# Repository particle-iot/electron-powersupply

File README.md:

Electron Power Management
---
[Place to host the experimental power supply design files for the Electron]

> To put it simply, the challenge in designing the power supply unit for the Electron is _supply and demand_. 

A cellular module is a power hungry device. Unlike WiFi, a GSM module requires a higher burst of power during transmission. These power/current spikes can go as high as 2Amps. This clearly exceeds USB's limit of 500mA in most cases. When developing on the Electron connected to a computer, care must be taken not to exceed the USB's limit while maintaining uninterrupted power to the cellular module. Most portable devices overcome this by having a battery connected at all times, like mobile phones. For a device like the Electron, it becomes essential to have the flexibility to power it either via the USB, battery or both.

The USB powered GSM modems currently available in the market use a switch-mode DC regulator with a high capacity bulk capacitor at the output. This capacitor stores enough energy to power the GSM module during its peak power requirements. At the same time, the regulator makes sure not to exceed the 500mA limit of draw current from a USB port. Most of the USB ports on today's computers are capable of sourcing 1Amp of continuous current. This allows for the use of a smaller bulk capacitor, but you still need to use one.

Things get a little interesting when you consider that 2G and 3G power requirements are completely different. The main difference is that a 2G TX burst will consume upto 2Amp of peak current, while in 3G burst is more controllable and flat with a peak requirement of 0.8A.

**Potential setup for the power unit:**

**Requirements for the PMC:**
 - Programmable input current limit
 - Built-in charger for 3.7V LiPo
 - Ouput current of minimum 1A
 - Power path management (optional)
 - Build-in switcher (optional)
 - Small footprint

**List of ICs under evaluation:**
- [BQ24298] (http://www.ti.com/lit/ds/symlink/bq24298.pdf) complete PMC from TI
- [LTC3567] (http://cds.linear.com/docs/en/datasheet/3567f.pdf) compete PMC from LT
- [BQ24030] (http://www.ti.com/lit/ds/symlink/bq24030.pdf) complete PMC - currently used on the power shield
- [TPS62750] (http://www.ti.com/lit/ds/symlink/tps62750.pdf) only a regulator

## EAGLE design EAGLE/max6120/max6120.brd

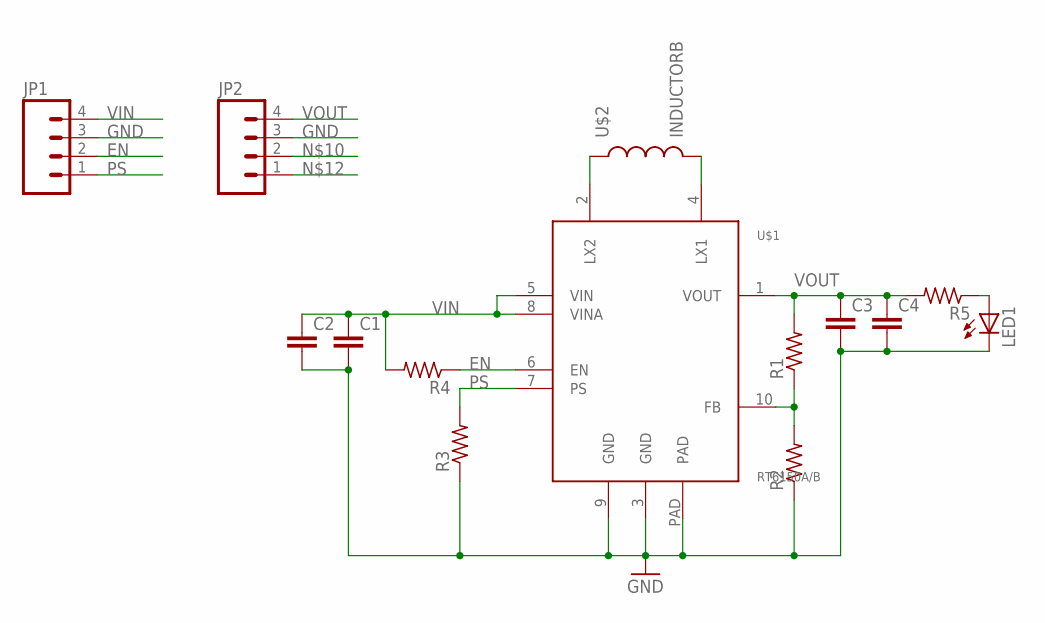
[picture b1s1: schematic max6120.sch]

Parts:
C1, C2, C3, C4: C-EUC0603; C0603
JP1, JP2: M041X04_NO_SILK; 1X04_NO_SILK
LED1: LEDCHIP-LED0603; CHIP-LED0603
R1, R2, R3, R4, R5: R-US_R0402; R0402
U$1: RT6150A/B; DFN3X310L
U$2: INDUCTORB; INDUCTOR-NR3015

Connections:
EN: JP1.2, R4.1, U$1.6 (EN)
GND: C1.2, C2.2, C3.2, C4.2, JP1.3, JP2.3, LED1.C, R2.1, R3.1, U$1.3 (GND), U$1.9 (GND), U$1.PAD
unnamed: U$1.2 (LX2), U$2.1
unnamed: U$1.4 (LX1), U$2.2
unnamed: R1.1, R2.2, U$1.10 (FB)
unnamed: LED1.A, R5.1
PS: JP1.1, R3.2, U$1.7 (PS)
VIN: C1.1, C2.1, JP1.4, R4.2, U$1.5 (VIN), U$1.8 (VINA)
VOUT: C3.1, C4.1, JP2.4, R1.2, R5.2, U$1.1 (VOUT)

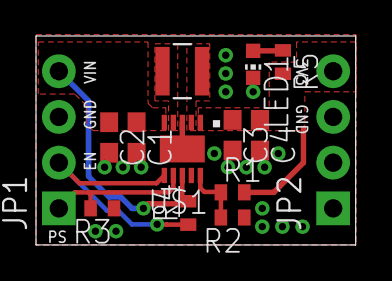
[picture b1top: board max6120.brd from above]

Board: 2 copper layers, 17.8 x 11.6 mm, 15 parts (0 on the bottom side), 9 nets.

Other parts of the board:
U$3: SPARK_LOGO2

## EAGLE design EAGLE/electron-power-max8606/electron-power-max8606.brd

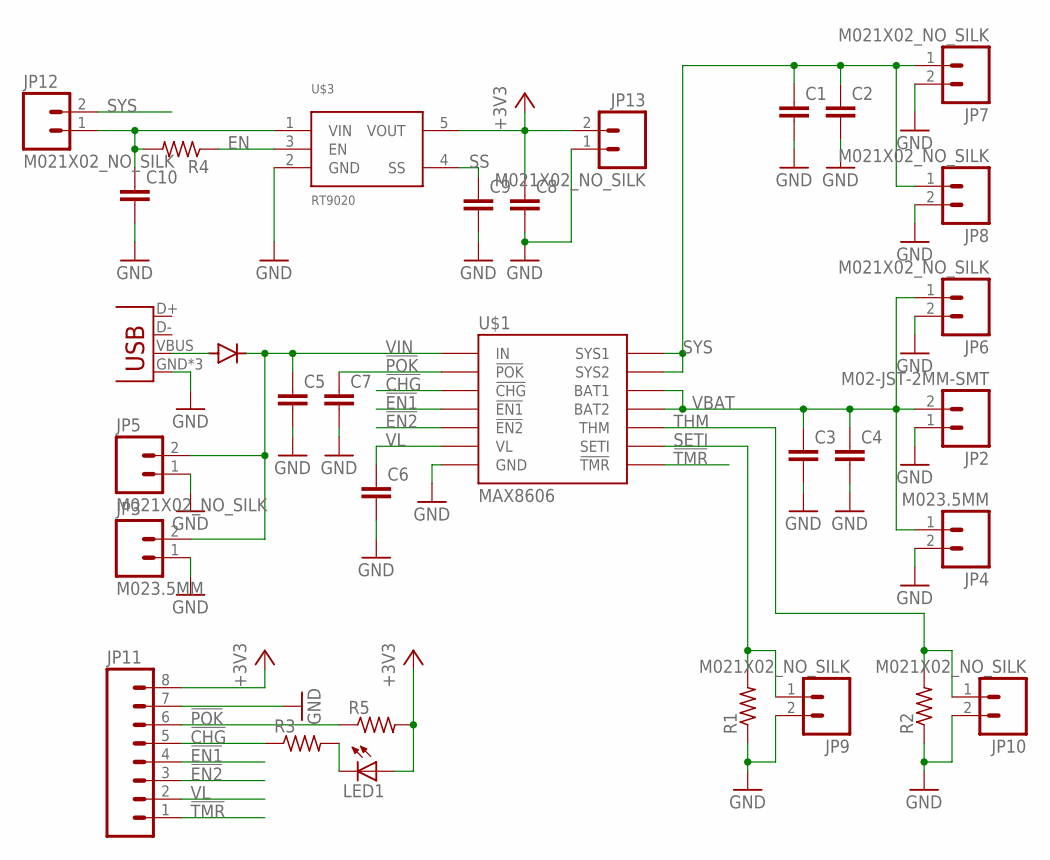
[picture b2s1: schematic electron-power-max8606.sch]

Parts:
C1, C2, C3, C4, C5: C-EUC0805; C0805
C6, C7, C8, C9, C10: C-EUC0402; C0402
JP1: USBUSB-MICROB-SLOT-HOLE; USB-MICROB-SLOT-HOLE
JP2: M02-JST-2MM-SMT; JST-2-SMD
JP3, JP4: M023.5MM; SCREWTERMINAL-3.5MM-2
JP5, JP6, JP7, JP8, JP9, JP10, JP12, JP13: M021X02_NO_SILK; 1X02_NO_SILK
JP11: M08; 1X08_PIN1_NO_SILK
LED1: LEDSML0805; SML0805
R1, R2, R3, R4, R5: R-US_R0402; R0402
U$1: MAX8606; TDFN-14
U$2: DIODE; DIODE-DO-220AA(SMP)
U$3: RT9020; SOT23-5

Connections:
!CHG: JP11.5, R3.1, U$1.P$6 (!CHG)
!EN1: JP11.4, U$1.P$10 (!EN1)
!EN2: JP11.3, U$1.P$9 (!EN2)
!POK: C7.1, JP11.6, R5.1, U$1.P$7 (!POK)
!TMR: JP11.1, U$1.P$8 (!TMR)
+3V3: C8.1, JP11.8, JP13.2, LED1.A, R5.2, U$3.5 (VOUT)
EN: R4.1, U$3.3 (EN)
GND: C1.2, C2.2, C3.2, C4.2, C5.2, C6.2, C7.2, C8.2, C9.2, C10.2, JP1.GND, JP1.MT1 (GND), JP1.MT2 (GND), JP2.1 (2), JP3.1, JP4.2, JP5.1, JP6.2, JP7.2, JP8.2, JP9.2, JP10.2, JP11.7, JP13.1, R1.1, R2.1, U$1.P$11 (GND), U$3.2 (GND)
unnamed: JP1.VBUS, U$2.ANODE
unnamed: C10.1, JP12.1, R4.2, U$3.1 (VIN)
unnamed: LED1.C, R3.2
SETI: JP9.1, R1.2, U$1.P$12 (SETI)
SS: C9.1, U$3.4 (SS)
SYS: C1.1, C2.1, JP7.1, JP8.1, JP12.2, U$1.P$13 (SYS1), U$1.P$14 (SYS2)
THM: JP10.1, R2.2, U$1.P$5 (THM)
VBAT: C3.1, C4.1, JP2.2 (1), JP4.1, JP6.1, U$1.P$1 (BAT1), U$1.P$2 (BAT2)
VIN: C5.1, JP3.2, JP5.2, U$1.P$3 (IN), U$2.CATHODE
VL: C6.1, JP11.2, U$1.P$4 (VL)

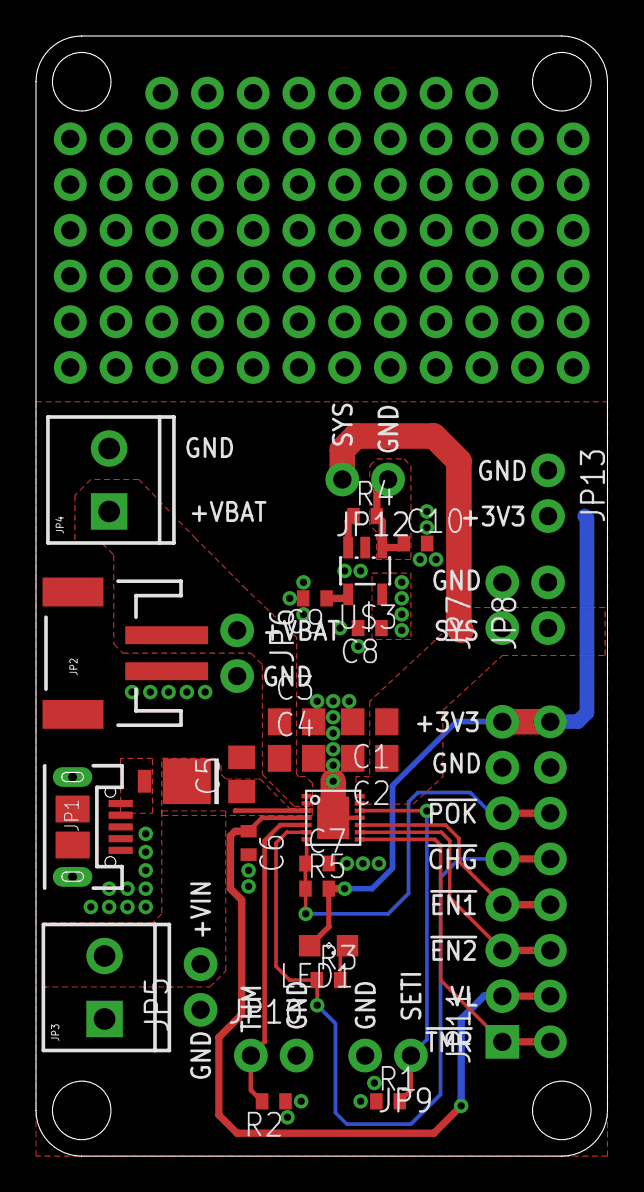
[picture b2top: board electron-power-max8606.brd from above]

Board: 2 copper layers, 31.8 x 62.2 mm, 32 parts (0 on the bottom side), 18 nets.

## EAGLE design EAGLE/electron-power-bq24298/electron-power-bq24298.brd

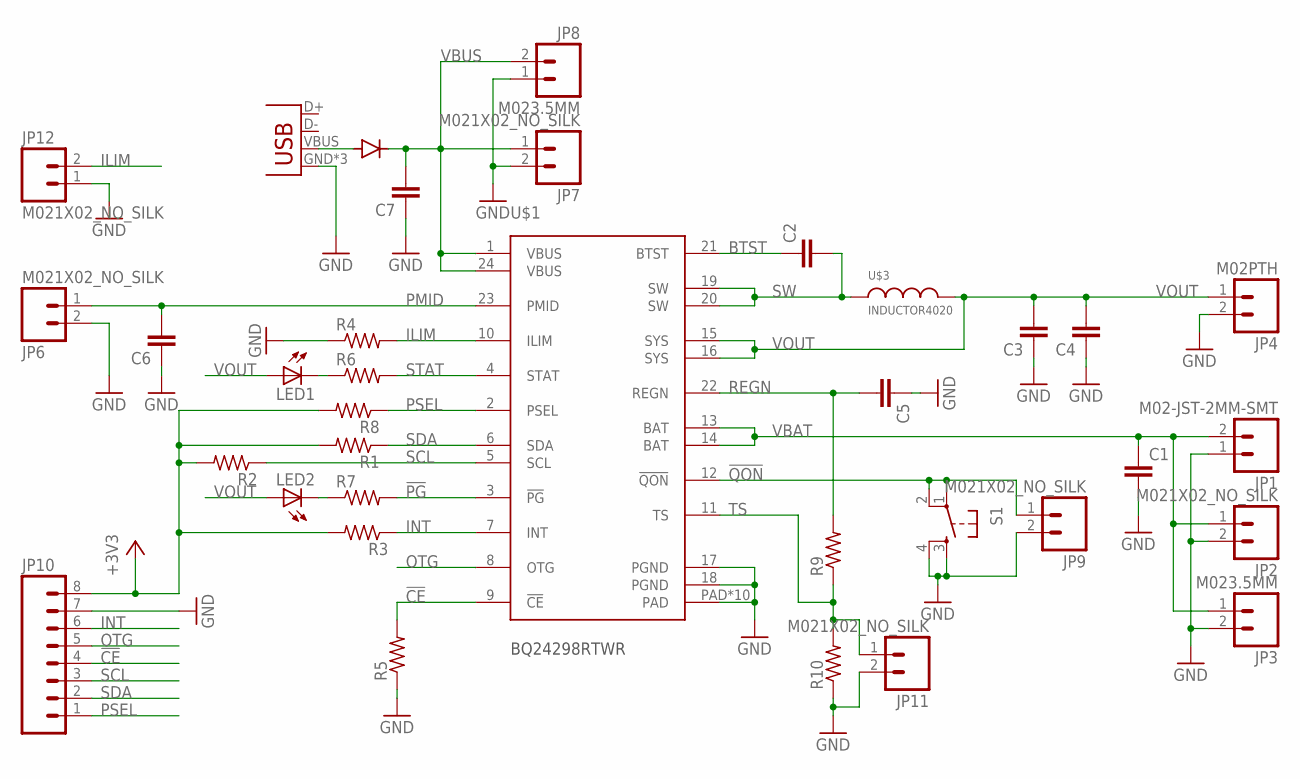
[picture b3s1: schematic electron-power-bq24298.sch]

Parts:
C1, C3, C4, C6, C7: C-EUC0805; C0805
C2, C5: C-EUC0402; C0402
JP1: M02-JST-2MM-SMT; JST-2-SMD
JP2, JP6, JP7, JP9, JP11, JP12: M021X02_NO_SILK; 1X02_NO_SILK
JP3, JP8: M023.5MM; SCREWTERMINAL-3.5MM-2
JP4: M02PTH; 1X02
JP5: USBUSB-MICROB-SLOT-HOLE; USB-MICROB-SLOT-HOLE
JP10: M08NO_SILK; 1X08_NO_SILK
LED1, LED2: LEDSML0805; SML0805
R1, R2, R3, R4, R5, R6, R7, R8, R9, R10: R-US_R0402; R0402
S1: TAC_SWITCHSMD; TACTILE_SWITCH_SMD
U$1: BQ24298RTWR; QFN24
U$2: DIODE; DIODE-DO-220AA(SMP)
U$3: INDUCTOR4020; 4020TYPE

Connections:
!CE: JP10.4, R5.2, U$1.9 (!CE)
!PG: R7.2, U$1.3 (!PG)
!QON: JP9.1, S1.1, S1.2, U$1.12 (!QON)
+3V3: JP10.8, R1.2, R2.2, R3.2, R8.2
BTST: C2.1, U$1.21 (BTST)
GND: C1.2, C3.1, C4.1, C5.1, C6.1, C7.1, JP1.1 (2), JP2.2, JP3.2, JP4.2, JP5.GND, JP5.MT1 (GND), JP5.MT2 (GND), JP6.2, JP7.2, JP8.1, JP9.2, JP10.7, JP11.2, JP12.1, R4.1, R5.1, R10.1, S1.3, S1.4, U$1.17 (PGND), U$1.18 (PGND), U$1.PAD, U$1.PAD@1 (PAD), U$1.PAD@2 (PAD), U$1.PAD@3 (PAD), U$1.PAD@4 (PAD), U$1.PAD@5 (PAD), U$1.PAD@6 (PAD), U$1.PAD@7 (PAD), U$1.PAD@8 (PAD), U$1.PAD@9 (PAD)
ILIM: JP12.2, R4.2, U$1.10 (ILIM)
INT: JP10.6, R3.1, U$1.7 (INT)
unnamed: JP5.VBUS, U$2.ANODE
unnamed: LED1.C, R6.1
unnamed: LED2.C, R7.1
OTG: JP10.5, U$1.8 (OTG)
PMID: C6.2, JP6.1, U$1.23 (PMID)
PSEL: JP10.1, R8.1, U$1.2 (PSEL)
REGN: C5.2, R9.2, U$1.22 (REGN)
SCL: JP10.3, R2.1, U$1.5 (SCL)
SDA: JP10.2, R1.1, U$1.6 (SDA)
STAT: R6.2, U$1.4 (STAT)
SW: C2.2, U$1.19 (SW), U$1.20 (SW), U$3.P$1 (1)
TS: JP11.1, R9.1, R10.2, U$1.11 (TS)
VBAT: C1.1, JP1.2 (1), JP2.1, JP3.1, U$1.13 (BAT), U$1.14 (BAT)
VBUS: C7.2, JP7.1, JP8.2, U$1.1 (VBUS), U$1.24 (VBUS), U$2.CATHODE
VOUT: C3.2, C4.2, JP4.1, LED1.A, LED2.A, U$1.15 (SYS), U$1.16 (SYS), U$3.P$2 (2)

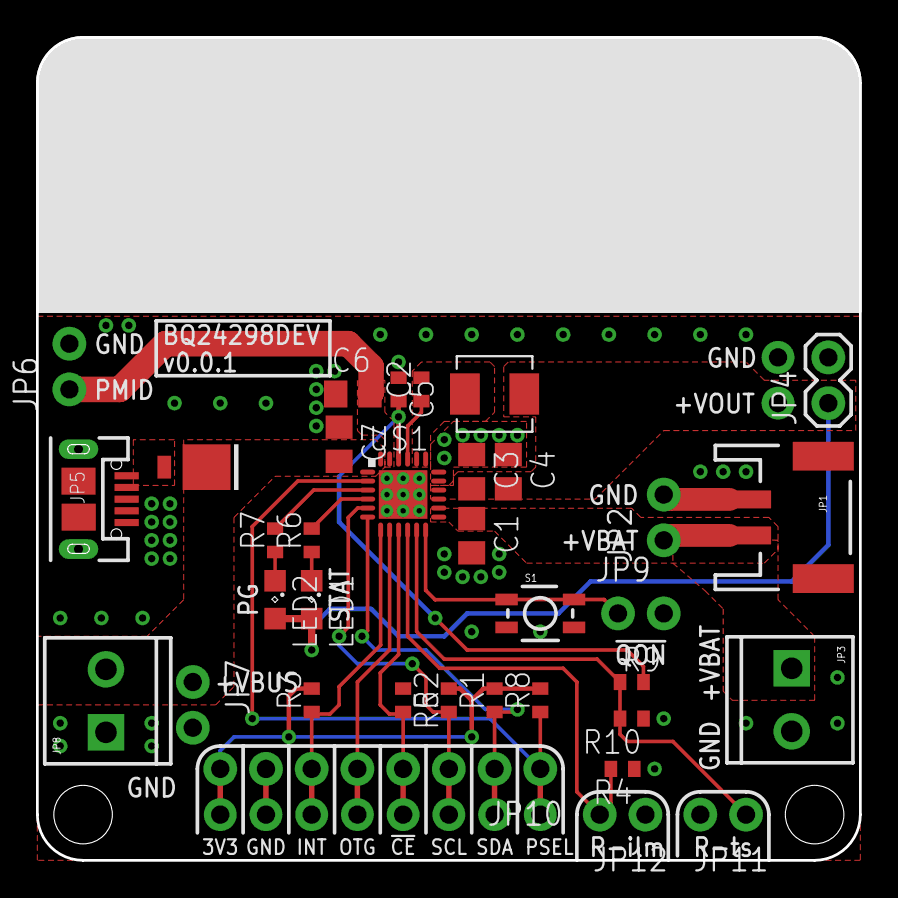
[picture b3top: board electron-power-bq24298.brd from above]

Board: 2 copper layers, 45.7 x 45.7 mm, 35 parts (0 on the bottom side), 23 nets.

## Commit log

2015-05-18 filled out readme
2015-05-18 added eagle files and ref docs
2015-05-18 updated image link
2015-05-18 added the projects log file
2015-05-19 added max8606 datasheet
2015-05-19 added pin labels
2015-05-19 generated gerber files
2015-05-19 gernerated gerbers for bq24298
2015-05-19 project log update
2015-05-19 fixed broken image link
2015-05-20 added max6120 based buck-boost board design and gerbers
    This is an evaluation breakout board based on the maxim MAX6120
    buck-boost regulator.
2018-01-03 org-rename
2025-08-20 Add CC-BY-SA license

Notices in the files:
parts and their libraries:
SparkFun-Connectors: Licensing: Creative Commons ShareAlike 4.0 International - https://creativecommons.org/licenses/by-sa/4.0
